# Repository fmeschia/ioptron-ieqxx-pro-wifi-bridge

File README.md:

# Wi-Fi to RS-232 bridge for iOptron iEQ Pro mounts

An ESP8266 and [esp-link](https://github.com/jeelabs/esp-link)-based Wi-Fi to RS-232 bridge to allow TCP wireless control of an iOptron iEQ Pro mount (tested on iEQ45 Pro, should also work on iEQ30 Pro).

[Here](https://www.youtube.com/watch?v=_uhQ0Lzc3-E) you can find a video of the operation an iEQ45 Pro mount with this circuit and the commercial Sky Safari app.

## Features
* Uses an inexpensive ESP8266 ESP-01 module
* Uses the well tested [esp-link](https://github.com/jeelabs/esp-link) open source firmware to implement a transparent TCP-to-serial bridge
* Powered directly from the mount, via the iOptron port, with an efficient 3.3V DC-to-DC converter based on the MC34063 switch-mode converter
* RS-232 compatibility ensured by a MAX3232 driver/receiver
* Easy to build, with through-hole parts and protoboard-friendly design

## Disclaimer
This project comes with no warranty. The project files may contain mistakes and errors. If you build this circuit, it is solely your responsibility to make sure that it doesn't damage your mount or other equipment, and doesn't hurt you or other people. Test all voltages and polarities before making any connections. By building the circuit you accept that I will have no liability whatsoever for damages or injuries that you or other parties may incur in during the building process or during the operation of the circuit. Builder assumes all risks. Don't build this circuit if you don't agree!

## Building instructions
### 1. Flash the ESP-01 module
The ESP-01 module must be flashed with the esp-link firmware. I have tested version 2.2.3 and it works well.
In order to flash the module, I recommend following the instructions present on the [release page](https://github.com/jeelabs/esp-link/releases/tag/v2.2.3) of the esp-link GitHub repository. Remember to enable flash programming mode by tying GPIO0 to ground and rebooting the module, before trying to upload the firmware code. The following is a schematic of how one should connect the ESP-01 module to a FTDI232 3.3V breakout board like the one sold by Sparkfun:

In my case, I used a 8-Mbit ESP-01 module, and in order to flash it (from a macOS system) I first installed esptool 1.1:

    $ curl -L https://github.com/themadinventor/esptool/archive/v1.1.tar.gz | tar xzf -
    $ cd esptool-1.1
    $ sudo python setup.py install

And then I used the following commands:

    $ curl -L https://github.com/jeelabs/esp-link/releases/download/v2.2.3/esp-link-v2.2.3.tgz | tar xzf -
    $ cd esp-link-v2.2.3
    $ esptool.py --port /dev/tty.usbserial-A601LLNU --baud 460800 write_flash -fs 8m -ff 40m 0x00000 boot_v1.5.bin 0x1000 user1.bin 0x7E000 blank.bin
    esptool.py v1.1
    Connecting...
    Running Cesanta flasher stub...
    Flash params set to 0x0020
    Writing 4096 @ 0x0... 4096 (100 %)
    Wrote 4096 bytes at 0x0 in 0.1 seconds (292.3 kbit/s)...
    Writing 307200 @ 0x1000... 307200 (100 %)
    Wrote 307200 bytes at 0x1000 in 7.1 seconds (347.0 kbit/s)...
    Writing 4096 @ 0x7e000... 4096 (100 %)
    Wrote 4096 bytes at 0x7e000 in 0.1 seconds (298.3 kbit/s)...
    Leaving...

### 2. Configure the esp-link bridge
After successfully flashing the ESP8266 module, you should power it down, remove the connection from GPI0 to ground, then power it up again and configure it. I recommend *not* powering it from USB via the FTDI232 board for this, because it doesn't really supply enough current for the ESP8266 in normal operation. Instead, power it from a regulated 3.3V (*not* 5V, it would burn it instantly!) power supply capable of delivering 0.5A.
Once powered up, a new Wi-Fi network with name "ESP_xxxx" should be visible. After connecting to that network, point your browser to http://192.168.4.1. If everything works fine, the browser should show the esp-link web interface. As a bare minimum, there are three configuration steps to do:

1. Configure the pin preset to "esp-01" 

2. Configure the serial port to 9600 bps, 8 data bits, 1 stop bit, no parity (9600 8N1) 

3. Disable the UART debug log 

You will also probably want to change the WiFi network name and its security, but that's up to personal preference.

### 3. Build the circuit
The EAGLE board file is easy to follow and transfer to a protoboard. The "traces" on the bottom layer are meant to be solder bridges between adjacent copper pads of the protoboard, whereas the air wires are meant to be real jumper wires. When the wire connects directly to a part lead, it is meant to be routed on the bottom of the board. When there are vias, the idea is that the wire can be routed on the top of the board, but of course that's just a suggestion.

The project also includes an Eagle file for a simple through-hole-parts PCB. It is essentially a single-sided board: all the traces are routed on the solder side, and the component side has just a ground plane. The ground plane, on both sides, stops short of the ESP8266 trace antenna.

## Usage
### Connection
To connect the circuit to the mount, you need to use two cords: 
* a "straight" 6P6C cord to connect the circuit to the iOptron port on the mount (for 12V power)
* a "straight" 4P4C cord to connect the circuit to the RS-232 port on the mount

"Straight" cords are cords in which the order of the colors of the inner wires is the same if you look at both plugs (when observed from the same side). The coiled cords that came with the mount came are straight cords:

*A 6P6C straight cord*
### Power it up
The bridge draws power directly from the mount. When the mount is powered up, the board is also energized and the LED should light up.
### Test it
If you have a digital mixed-signal oscilloscope, you can test if the board works properly by capturing the output of the RXD pin of the RS-232 port while connected to the ESP8266 Wi-Fi AP and while sending a string to the TCP port 23 of the ESP8266 IP address (by default, 192.168.4.1). Here is a sample screenshot of the output of a USB logic analyzer while sending the string "HELLO" (ASCII 0x48 0x45 0x4C 0x4C 0x4F plus a 0x0A newline) to the bridge board:

### Enjoy!
Point your favorite telescope control software to 192.168.4.1, port 23, and enjoy wireless telescope control!

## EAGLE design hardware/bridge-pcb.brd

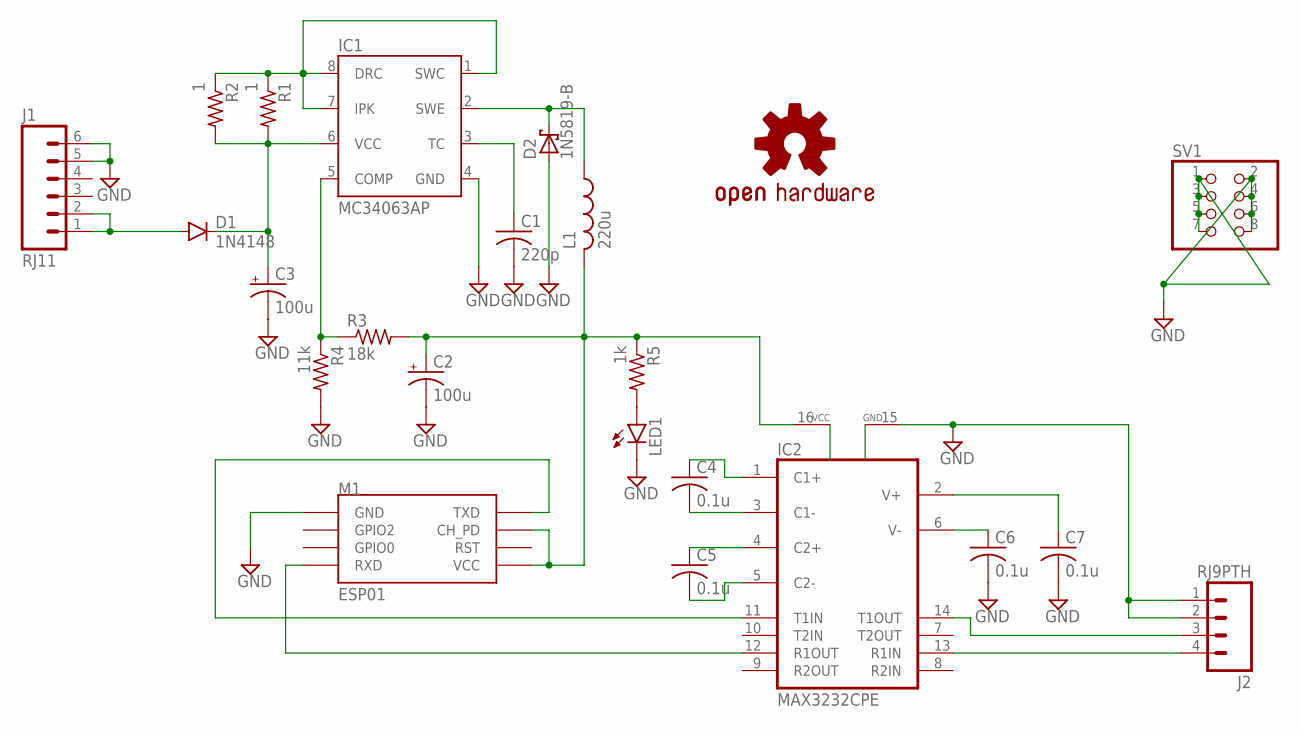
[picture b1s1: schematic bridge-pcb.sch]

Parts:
C1: 220p; C025-024X044
C2, C3: 100u; E2,5-5
C4, C5, C6, C7: 0.1u; C025-024X044
D1: 1N4148; DIODE-1N4148
D2: 1N5819-B; DO41-7.6
IC1: MC34063AP; DIL-08
IC2: MAX3232CPE; DIL16
J1: RJ11; RJ11-6
J2: RJ9PTH; RJ9
L1: 220u; 6000-XXXX-RC
LED1: LED5MM
LOGO1: OSHW-LOGOM; OSHW-LOGO-M
M1: ESP01
R1, R2: 1; 0204V
R3: 18k; 0204V
R4: 11k; 0204V
R5: 1k; 0204/7
SV1: PINHD-2X4; 2X04

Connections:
3V3: C2.+, IC2.16 (VCC), L1.2, M1.CH_PD, M1.VCC, R3.2, R5.1
12V: C3.+, D1.C, IC1.6 (VCC), R1.2, R2.2
GND: C1.2, C2.-, C3.-, C6.2, C7.2, D2.A, IC1.4 (GND), IC2.15 (GND), J1.5, J1.6, J2.1, J2.2, LED1.K (C), M1.GND, R4.2, SV1.1, SV1.2, SV1.3, SV1.4, SV1.5, SV1.6, SV1.7, SV1.8
unnamed: C1.1, IC1.3 (TC)
unnamed: LED1.A, R5.2
unnamed: D2.C, IC1.2 (SWE), L1.1
unnamed: IC2.11 (T1IN), M1.TX (TXD)
unnamed: IC2.12 (R1OUT), M1.RX (RXD)
unnamed: C4.2, IC2.3 (C1-)
unnamed: C4.1, IC2.1 (C1+)
unnamed: C5.1, IC2.4 (C2+)
unnamed: C5.2, IC2.5 (C2-)
unnamed: C6.1, IC2.6 (V-)
unnamed: C7.1, IC2.2 (V+)
unnamed: IC2.14 (T1OUT), J2.3
unnamed: IC2.13 (R1IN), J2.4
unnamed: IC1.1 (SWC), IC1.7 (IPK), IC1.8 (DRC), R1.1, R2.1
unnamed: IC1.5 (COMP), R3.1, R4.1
VBATT: D1.A, J1.1, J1.2

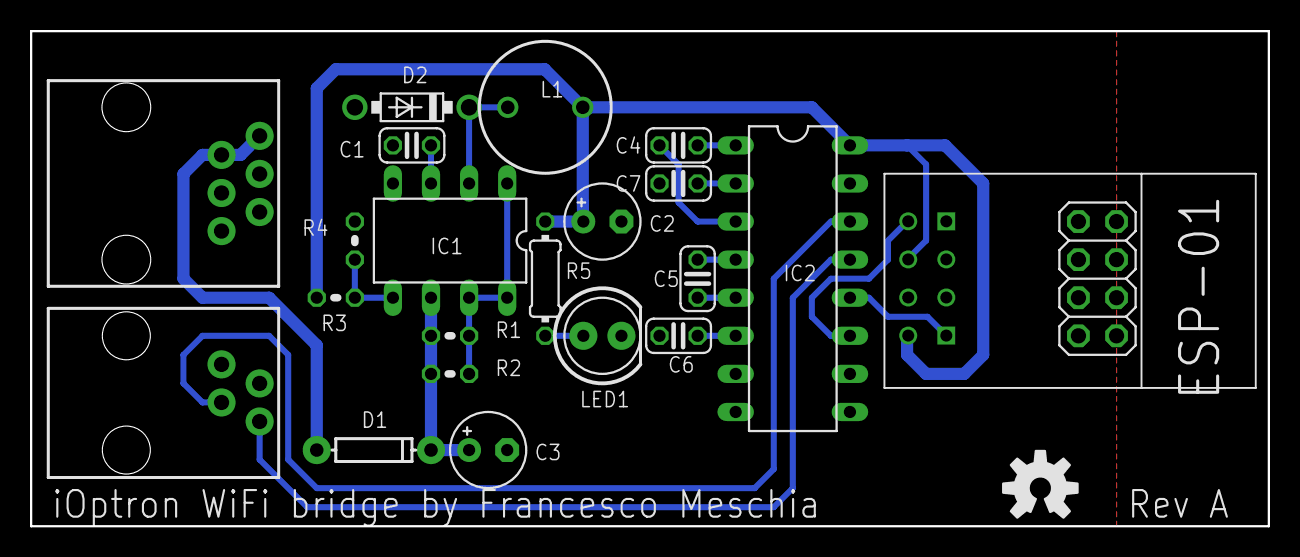
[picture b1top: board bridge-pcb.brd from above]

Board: 2 copper layers, 82.5 x 33.0 mm, 23 parts (0 on the bottom side), 19 nets.

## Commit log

2016-07-30 Documentation changes
2016-07-30 Minor design and documentation changes
2016-07-30 Minor board beauty treatment
2016-11-14 Small board changes
2016-12-30 Doc changes. Added one-layer PCB ready for fabrication (e.g. via OSH Park).
2016-12-30 Minor correction to docs
2017-01-09 Minor changes in docs
2017-01-14 Tweaked fonts and layers in PCB
2017-01-21 Doc changes
2017-01-22 Minor doc changes
2017-01-23 Minor doc tweaks
2017-06-15 Edited Reame.md
    FIxed some markdown issues
2017-06-22 Added BOM
2017-09-04 Added pin header footprint to provide support for the ESP8266 module
2017-09-04 Edited readme.md
2017-09-04 Added pic files
2017-09-04 Added some documentation for esp-link flashing and configuration

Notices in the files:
parts and their libraries:
SparkFun-LED: Licensing: Creative Commons ShareAlike 4.0 International - https://creativecommons.org/licenses/by-sa/4.0
